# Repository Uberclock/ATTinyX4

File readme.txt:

NancyHacker is based on Logxen's ATTinyX4 breakout and is designed to allow easy reconfiguration of a NancyDriver.

Basic Operation:

1) Plug a NancyDriver into the NancyHacker and use a MicroUSB cable to supply power to the NancyHacker.

2) The LED on the NancyHacker will flash to read out the set current on the driver board in amps. First it will count out slow flashes (1 second on, 1 second off) representing the integer then short flashes (0.5 second on, 0.5 second off) representing the tenths. So, a brand new NancyDriver should arrive set to 1.2A and so should read one long flash followed by two short flashes and a pause.

3) The UP and DOWN buttons can be used to adjust the set current by tenths. The NancyHacker will then read out the new setting over the LED. That's all there is to it. :)

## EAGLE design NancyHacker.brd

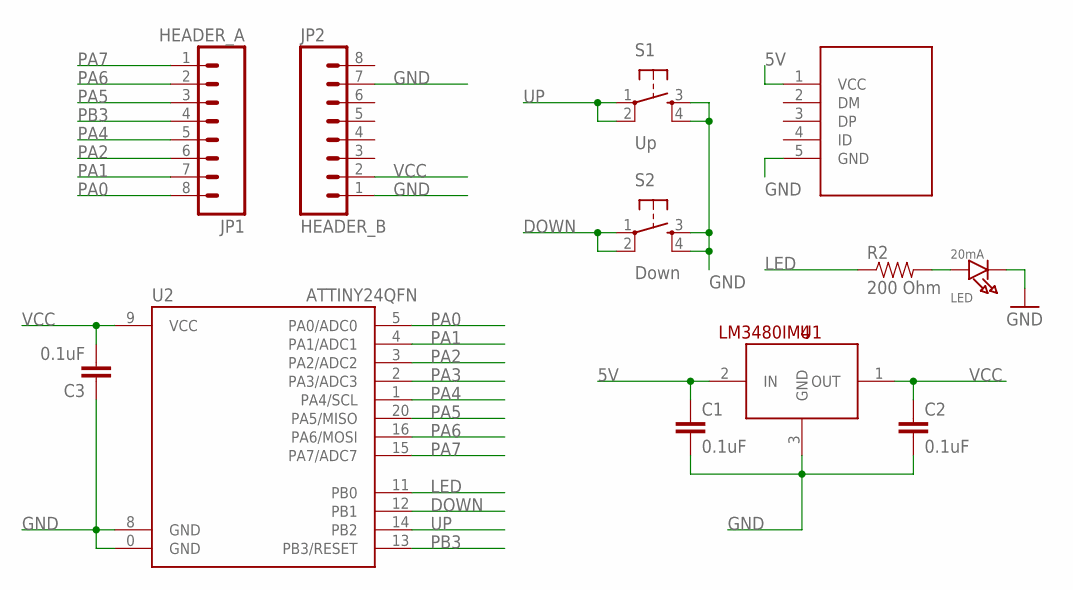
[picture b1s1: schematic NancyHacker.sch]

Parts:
C1, C2, C3: 0.1uF; 0603-CAP
JP1: HEADER_A; 1X08
JP2: HEADER_B; 1X08
LED: 20mA; CHIPLED_0603_NOOUTLINE
R2: 200 Ohm; 0402-RES
S1: Up; TACTILE_SWITCH_SMD
S2: Down; TACTILE_SWITCH_SMD
U1: LM3480IM4; SOT23-3
U2: ATTINY24QFN; QFN20
U$1: USB-MICROB-SMDRECEPT; USB-MICROB-RECEPT

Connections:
5V: C1.1, U1.2 (IN), U$1.1 (VCC)
DOWN: S2.1, S2.2, U2.12 (PB1)
GND: C1.2, C2.2, C3.1, JP2.1, JP2.7, LED.C, S1.3, S1.4, S2.3, S2.4, U1.3 (GND), U2.0 (GND), U2.8 (GND), U$1.5 (GND)
LED: R2.1, U2.11 (PB0)
PA0: JP1.8, U2.5 (PA0/ADC0)
PA1: JP1.7, U2.4 (PA1/ADC1)
PA2: JP1.6, U2.3 (PA2/ADC2)
PA3: U2.2 (PA3/ADC3)
PA4: JP1.5, U2.1 (PA4/SCL)
PA5: JP1.3, U2.20 (PA5/MISO)
PA6: JP1.2, U2.16 (PA6/MOSI)
PA7: JP1.1, U2.15 (PA7/ADC7)
PB3: JP1.4, U2.13 (PB3/RESET)
STATUS_LED_RESISTOR: LED.A, R2.2
UP: S1.1, S1.2, U2.14 (PB2)
VCC: C2.1, C3.2, JP2.2, U1.1 (OUT), U2.9 (VCC)

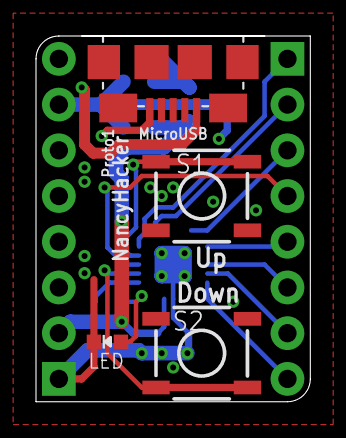
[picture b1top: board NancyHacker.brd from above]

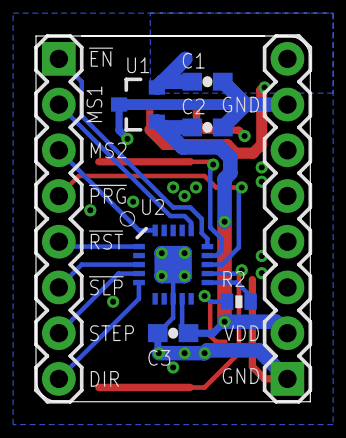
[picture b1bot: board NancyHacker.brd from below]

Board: 2 copper layers, 15.2 x 20.3 mm, 12 parts (8 on the bottom side), 15 nets.

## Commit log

2013-05-26 Renamed sch and brd files
2013-05-26 Initial commit of forked NancyHacker (Prototype 1)
2013-05-26 Added BoM
2013-05-26 Moved pcb files into hardware directory
2013-05-26 Added readme.txt
2013-05-27 Initial firmware implementation
    still waiting on prototype NancyDriver and NancyHacker pcbs so code has
    not been tested

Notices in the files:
parts and their libraries:
SparkFun-DigitalIC: Licensing: CC v3.0 Share-Alike You are welcome to use this library for commercial purposes.
microbuilder: This work is placed in the public domain, and may be freely used for commercial and non-commercial work with the following conditions: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
